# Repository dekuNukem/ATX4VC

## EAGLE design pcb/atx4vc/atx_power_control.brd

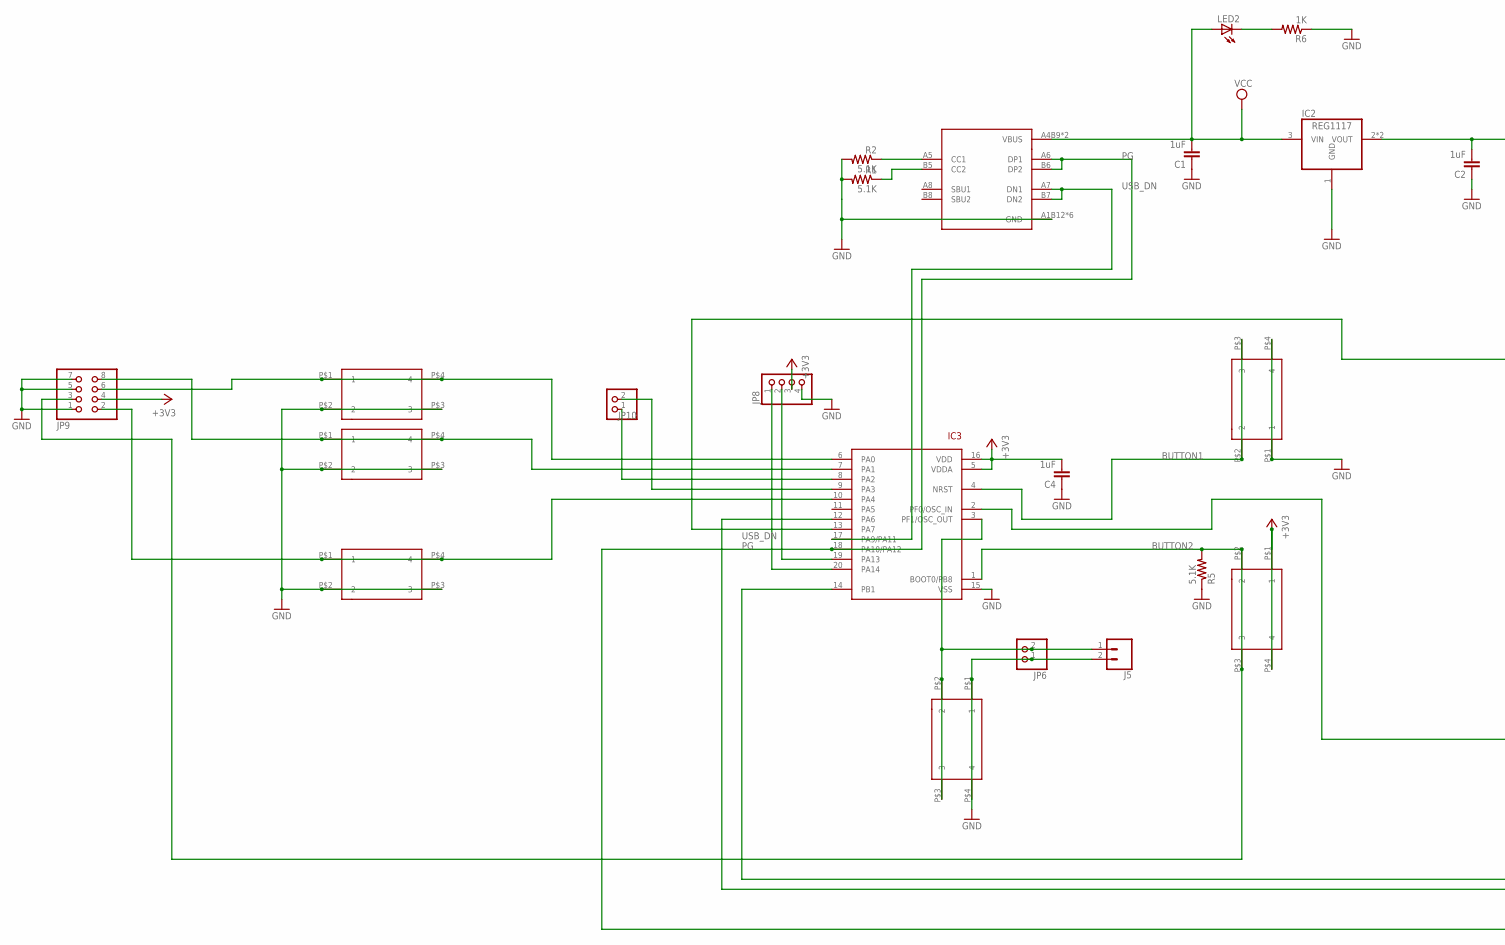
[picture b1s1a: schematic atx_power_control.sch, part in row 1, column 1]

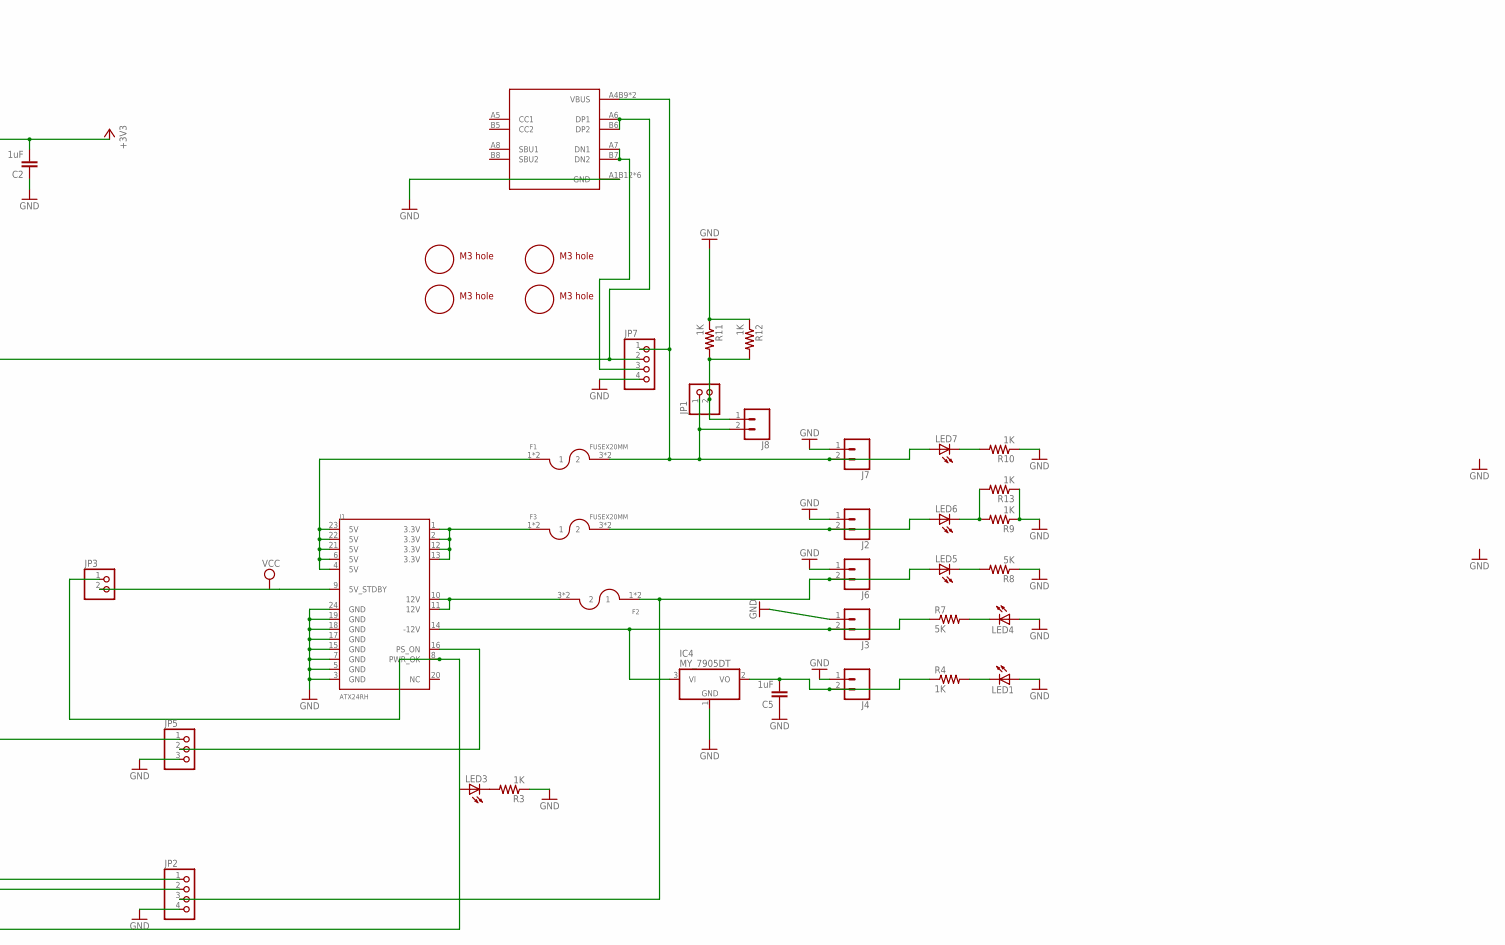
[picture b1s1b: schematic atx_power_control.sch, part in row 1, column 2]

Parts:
C1, C2, C4, C5: 1uF; 0805@1
F1, F2, F3: FUSEX20MM; FUSE_5MM
IC2: REG1117; SOT223
IC3: STM32F042F4; TSSOP20
IC4: MY_7905DT; ADAFRUIT_TO252
J1: ATX24RH; ATX24_RIGHT_ANGLE
J2, J3, J4, J5, J6, J8: CONN_023.5MM; SCREWTERMINAL-3.5MM-2
J7: CONN_023.5MM-NO_SILK; SCREWTERMINAL-3.5MM-2-NS
JP1, JP3, JP6, JP10: PINHD-1X2; 1X02
JP2, JP7, JP8: PINHD-1X4; 1X04
JP5: PINHD-1X3; 1X03
JP9: PINHD-2X4; 2X04
LED1, LED2, LED3, LED4, LED5, LED6, LED7: LEDCHIP-LED0805; CHIP-LED0805
R1, R2, R5: 5.1K; 0805
R3, R4, R6, R9, R10, R11, R12, R13: 1K; 0805
R7, R8: 5K; 0805
SW1, SW2, SW3, SW4, SW5, SW7: 324_SW; 342_SWICH_FOOT
U1, U2: USBC_16P; USBC_16P_FOOT
U$1, U$2, U$3, U$10: M3_MOUNTING_HOLE; M3_MOUNTING_HOLE_PACK

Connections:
+3V3: C2.2, C4.2, IC2.2 (VOUT), IC2.4 (VOUT), IC3.5 (VDDA), IC3.16 (VDD), JP8.3, JP9.4, SW4.P$1 (1), SW4.P$4 (4)
BUTTON1: IC3.4 (NRST), SW3.P$2 (2), SW3.P$3 (3)
BUTTON2: IC3.1 (BOOT0/PB8), JP9.3, R5.2, SW4.P$2 (2), SW4.P$3 (3)
GND: C1.1, C2.1, C4.1, C5.1, IC2.1 (GND), IC3.15 (VSS), IC4.1 (GND), J1.3 (GND), J1.5 (GND), J1.7 (GND), J1.15 (GND), J1.17 (GND), J1.18 (GND), J1.19 (GND), J1.24 (GND), J2.1, J3.1, J4.1, J5.2, J6.1, J7.1, JP2.4, JP5.3, JP6.1, JP7.4, JP8.4, JP9.1, JP9.5, JP9.7, LED1.A, LED4.A, R1.2, R2.2, R3.1, R5.1, R6.1, R8.1, R9.1, R10.1, R11.1, R12.1, R13.1, SW1.P$1 (1), SW1.P$4 (4), SW2.P$2 (2), SW2.P$3 (3), SW3.P$1 (1), SW3.P$4 (4), SW5.P$2 (2), SW5.P$3 (3), SW7.P$2 (2), SW7.P$3 (3), U1.A1B12 (GND), U1.B11A12 (GND), U1.P$13 (GND), U1.P$14 (GND), U1.P$15 (GND), U1.P$16 (GND), U2.A1B12 (GND), U2.B11A12 (GND), U2.P$13 (GND), U2.P$14 (GND), U2.P$15 (GND), U2.P$16 (GND)
unnamed: LED3.C, R3.2
unnamed: IC4.3 (VI), J1.14 (-12V), J3.2, R7.1
unnamed: IC3.20 (PA14), JP8.1
unnamed: IC3.19 (PA13), JP8.2
unnamed: LED1.C, R4.2
unnamed: IC3.12 (PA6), JP2.2
unnamed: IC3.14 (PB1), JP2.1
unnamed: LED4.C, R7.2
unnamed: LED5.C, R8.2
unnamed: F1.1, F1.2 (1), J1.4 (5V), J1.6 (5V), J1.21 (5V), J1.22 (5V), J1.23 (5V)
unnamed: C5.2, IC4.2 (VO), J4.2, R4.1
unnamed: IC3.9 (PA3), JP10.2
unnamed: IC3.6 (PA0), JP9.6, SW2.P$1 (1), SW2.P$4 (4)
unnamed: F3.1, F3.2 (1), J1.1 (3.3V), J1.2 (3.3V), J1.12 (3.3V), J1.13 (3.3V)
unnamed: F2.1, F2.2 (1), J6.2, JP2.3, LED5.A
unnamed: J8.1, JP1.2, R11.2, R12.2
unnamed: LED6.C, R9.2, R13.2
unnamed: F3.3 (2), F3.4 (2), J2.2, LED6.A
unnamed: LED7.C, R10.2
unnamed: F2.3 (2), F2.4 (2), J1.10 (12V), J1.11 (12V)
unnamed: IC3.7 (PA1), JP9.8, SW5.P$1 (1), SW5.P$4 (4)
unnamed: IC3.8 (PA2), JP10.1
unnamed: IC3.2 (PF0/OSC_IN), JP5.1
unnamed: J1.16 (PS_ON), JP5.2
unnamed: IC3.3 (PF1/OSC_OUT), J5.1, JP6.2, SW1.P$2 (2), SW1.P$3 (3)
unnamed: IC3.10 (PA4), JP9.2, SW7.P$1 (1), SW7.P$4 (4)
unnamed: LED2.C, R6.2
unnamed: F1.3 (2), F1.4 (2), J7.2, J8.2, JP1.1, JP7.1, LED7.A, U1.A4B9 (VBUS), U1.B4A9 (VBUS)
unnamed: R1.1, U2.B5 (CC2)
unnamed: R2.1, U2.A5 (CC1)
unnamed: IC3.13 (PA7), JP7.2, U1.A6 (DP1), U1.B6 (DP2)
unnamed: JP7.3, U1.A7 (DN1), U1.B7 (DN2)
PG: IC3.18 (PA10/PA12), J1.8 (PWR_OK), JP3.1, LED3.A, U2.A6 (DP1), U2.B6 (DP2)
USB_DN: IC3.17 (PA9/PA11), U2.A7 (DN1), U2.B7 (DN2)
VCC: C1.2, IC2.3 (VIN), J1.9 (5V_STDBY), JP3.2, LED2.A, U2.A4B9 (VBUS), U2.B4A9 (VBUS)

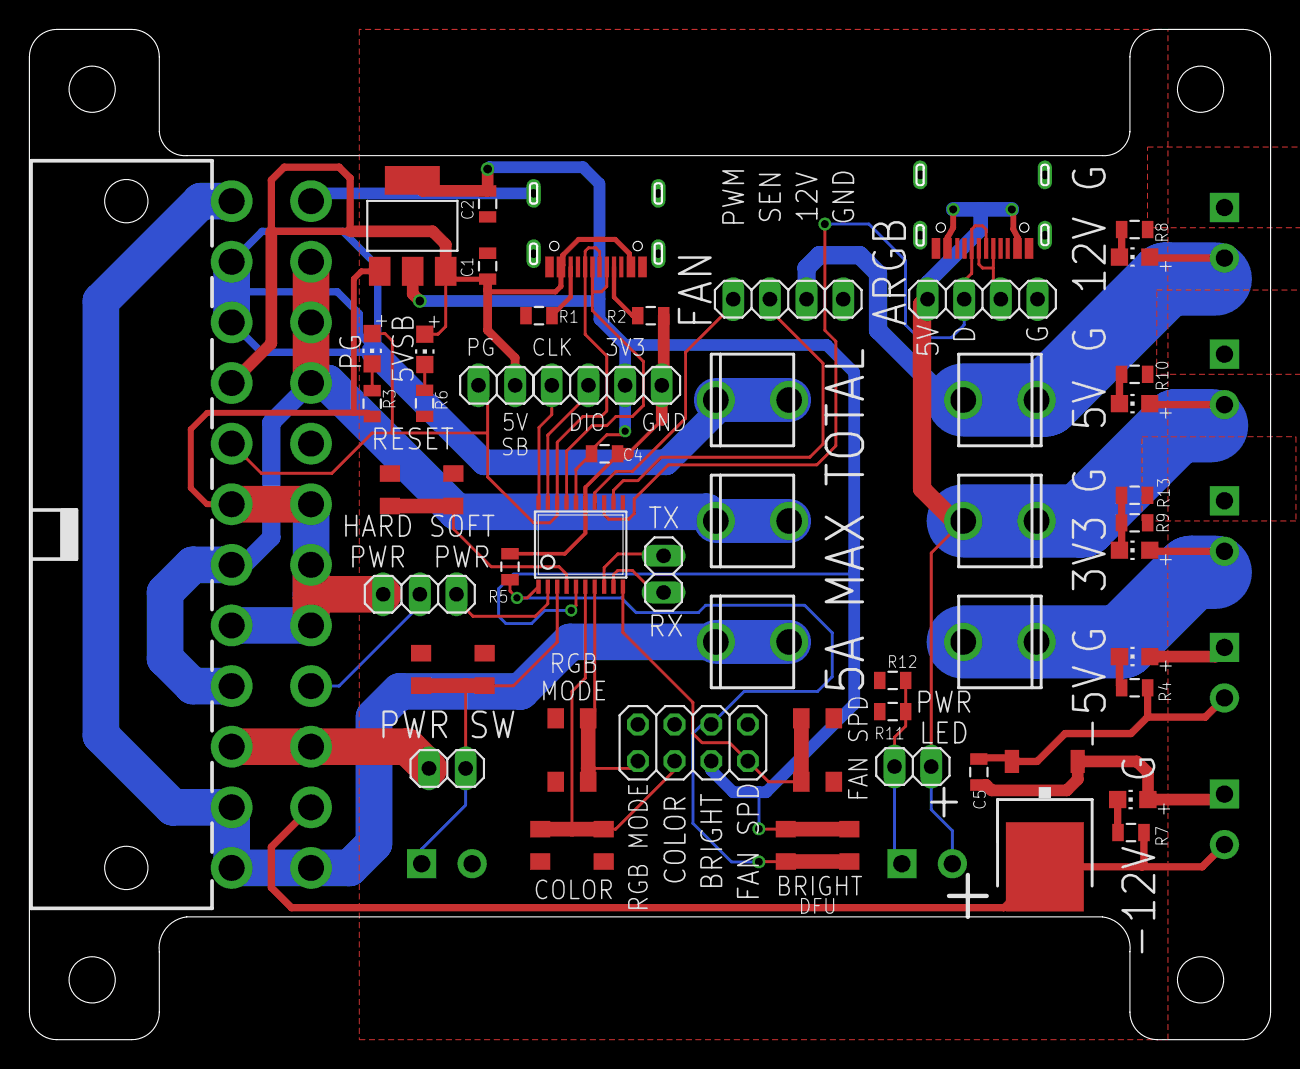
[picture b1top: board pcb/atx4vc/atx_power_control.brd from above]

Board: 2 copper layers, 86.0 x 70.0 mm, 59 parts (0 on the bottom side), 39 nets.

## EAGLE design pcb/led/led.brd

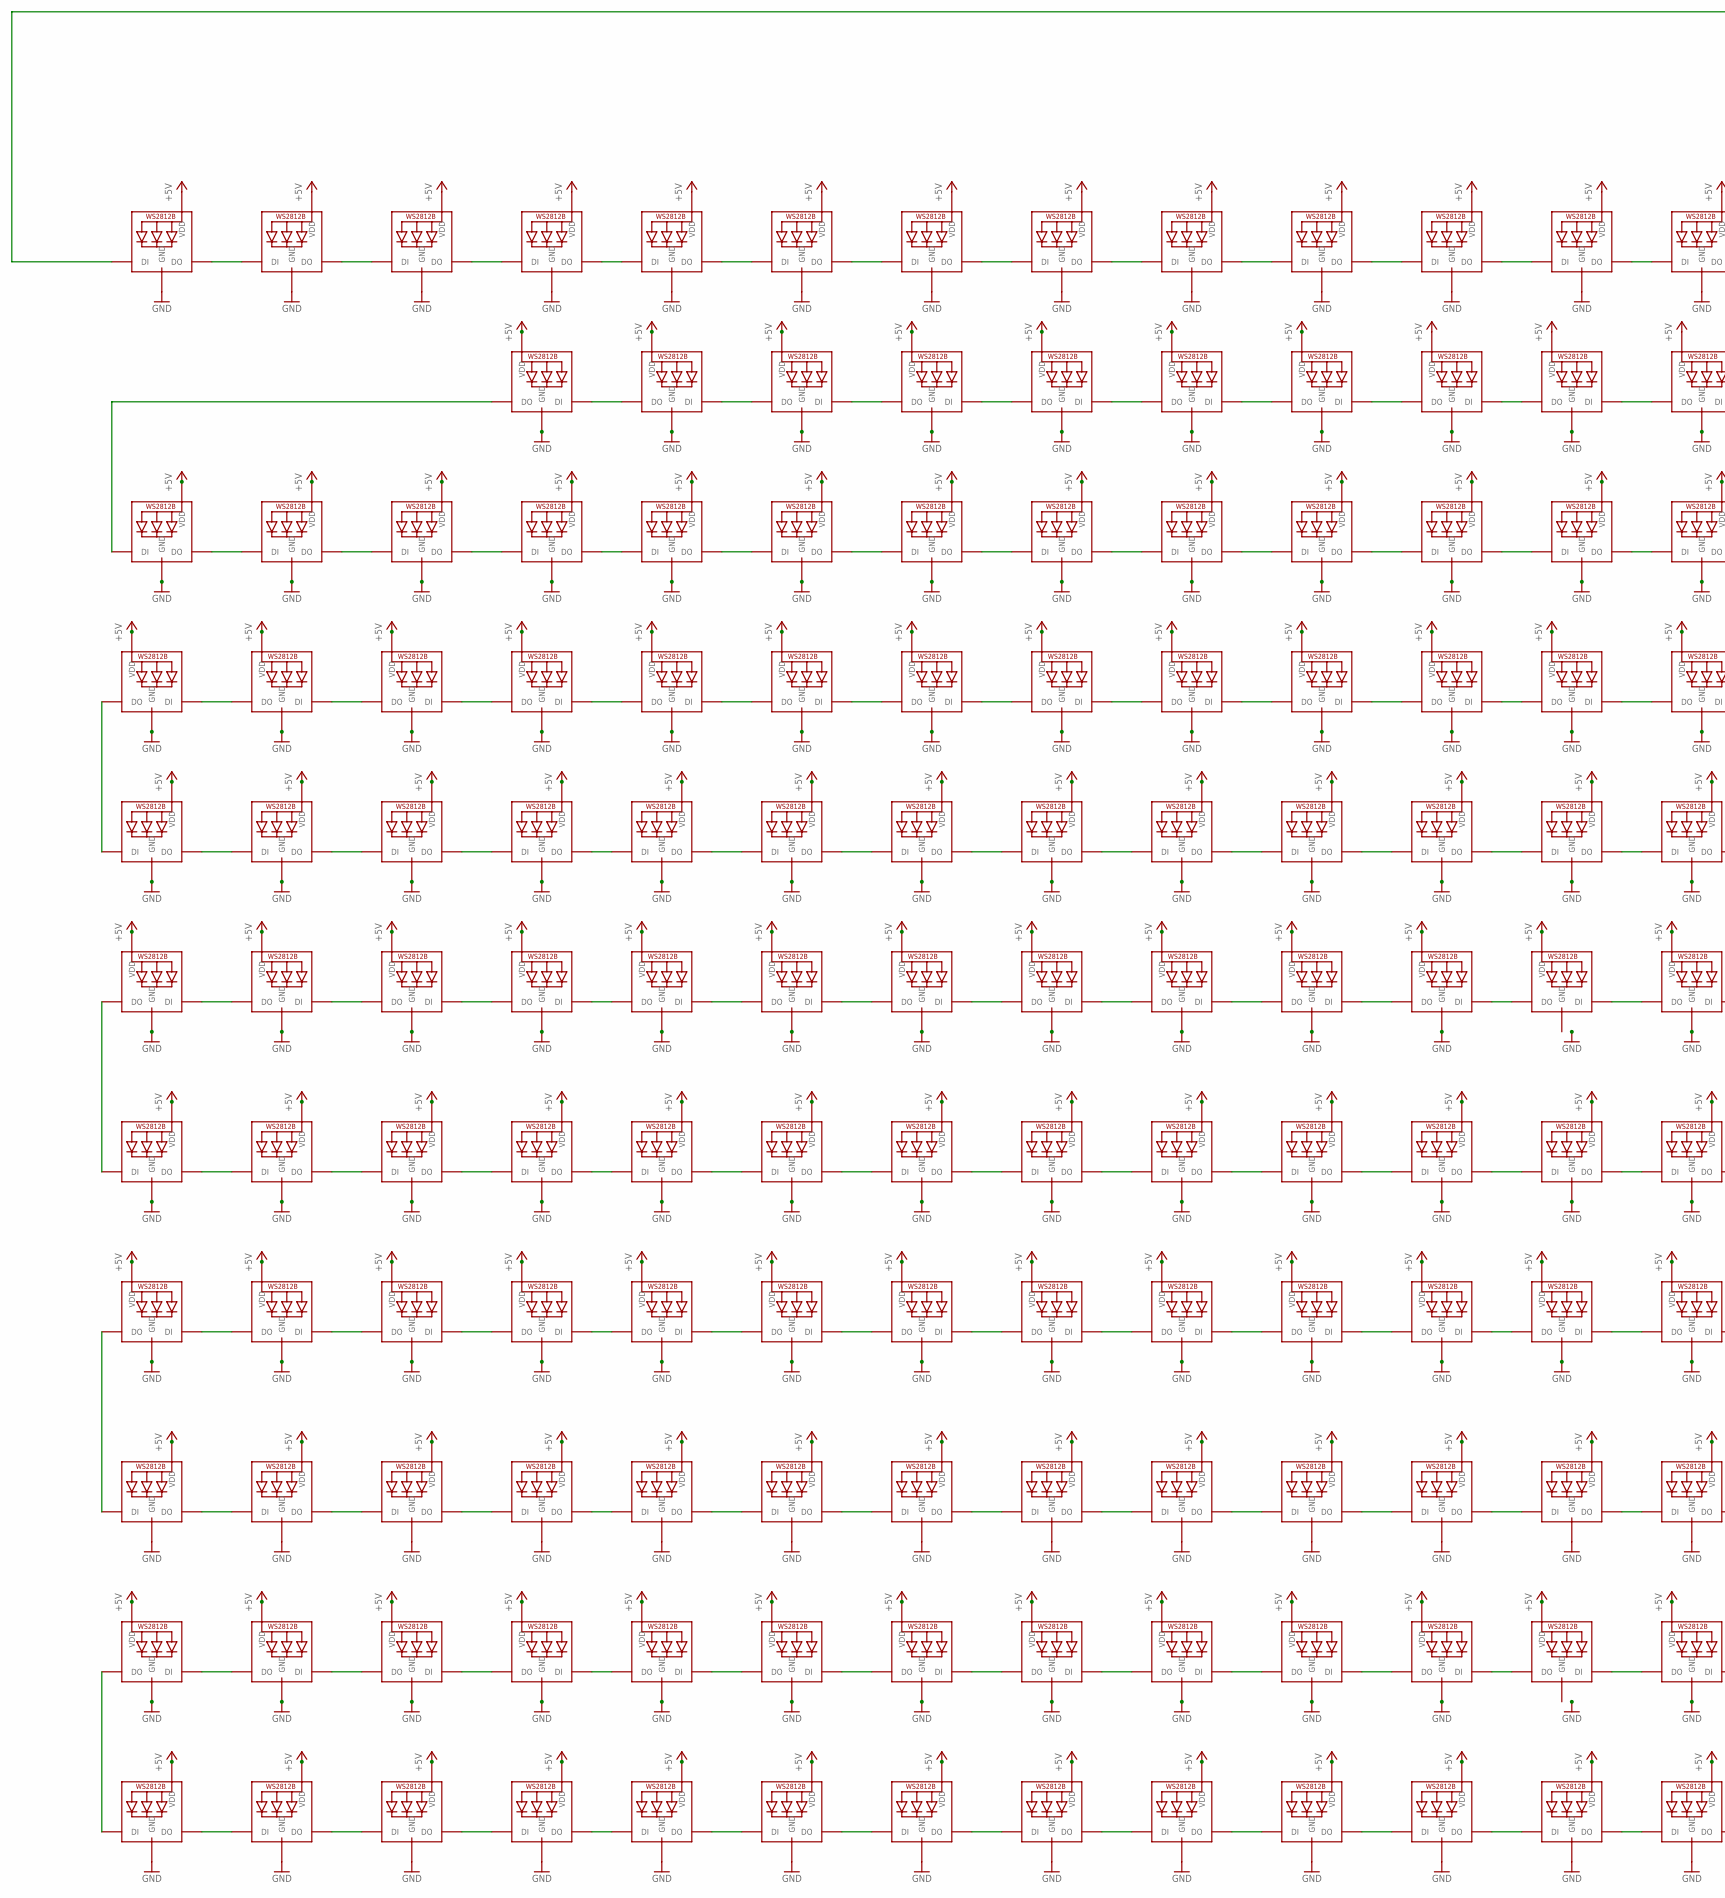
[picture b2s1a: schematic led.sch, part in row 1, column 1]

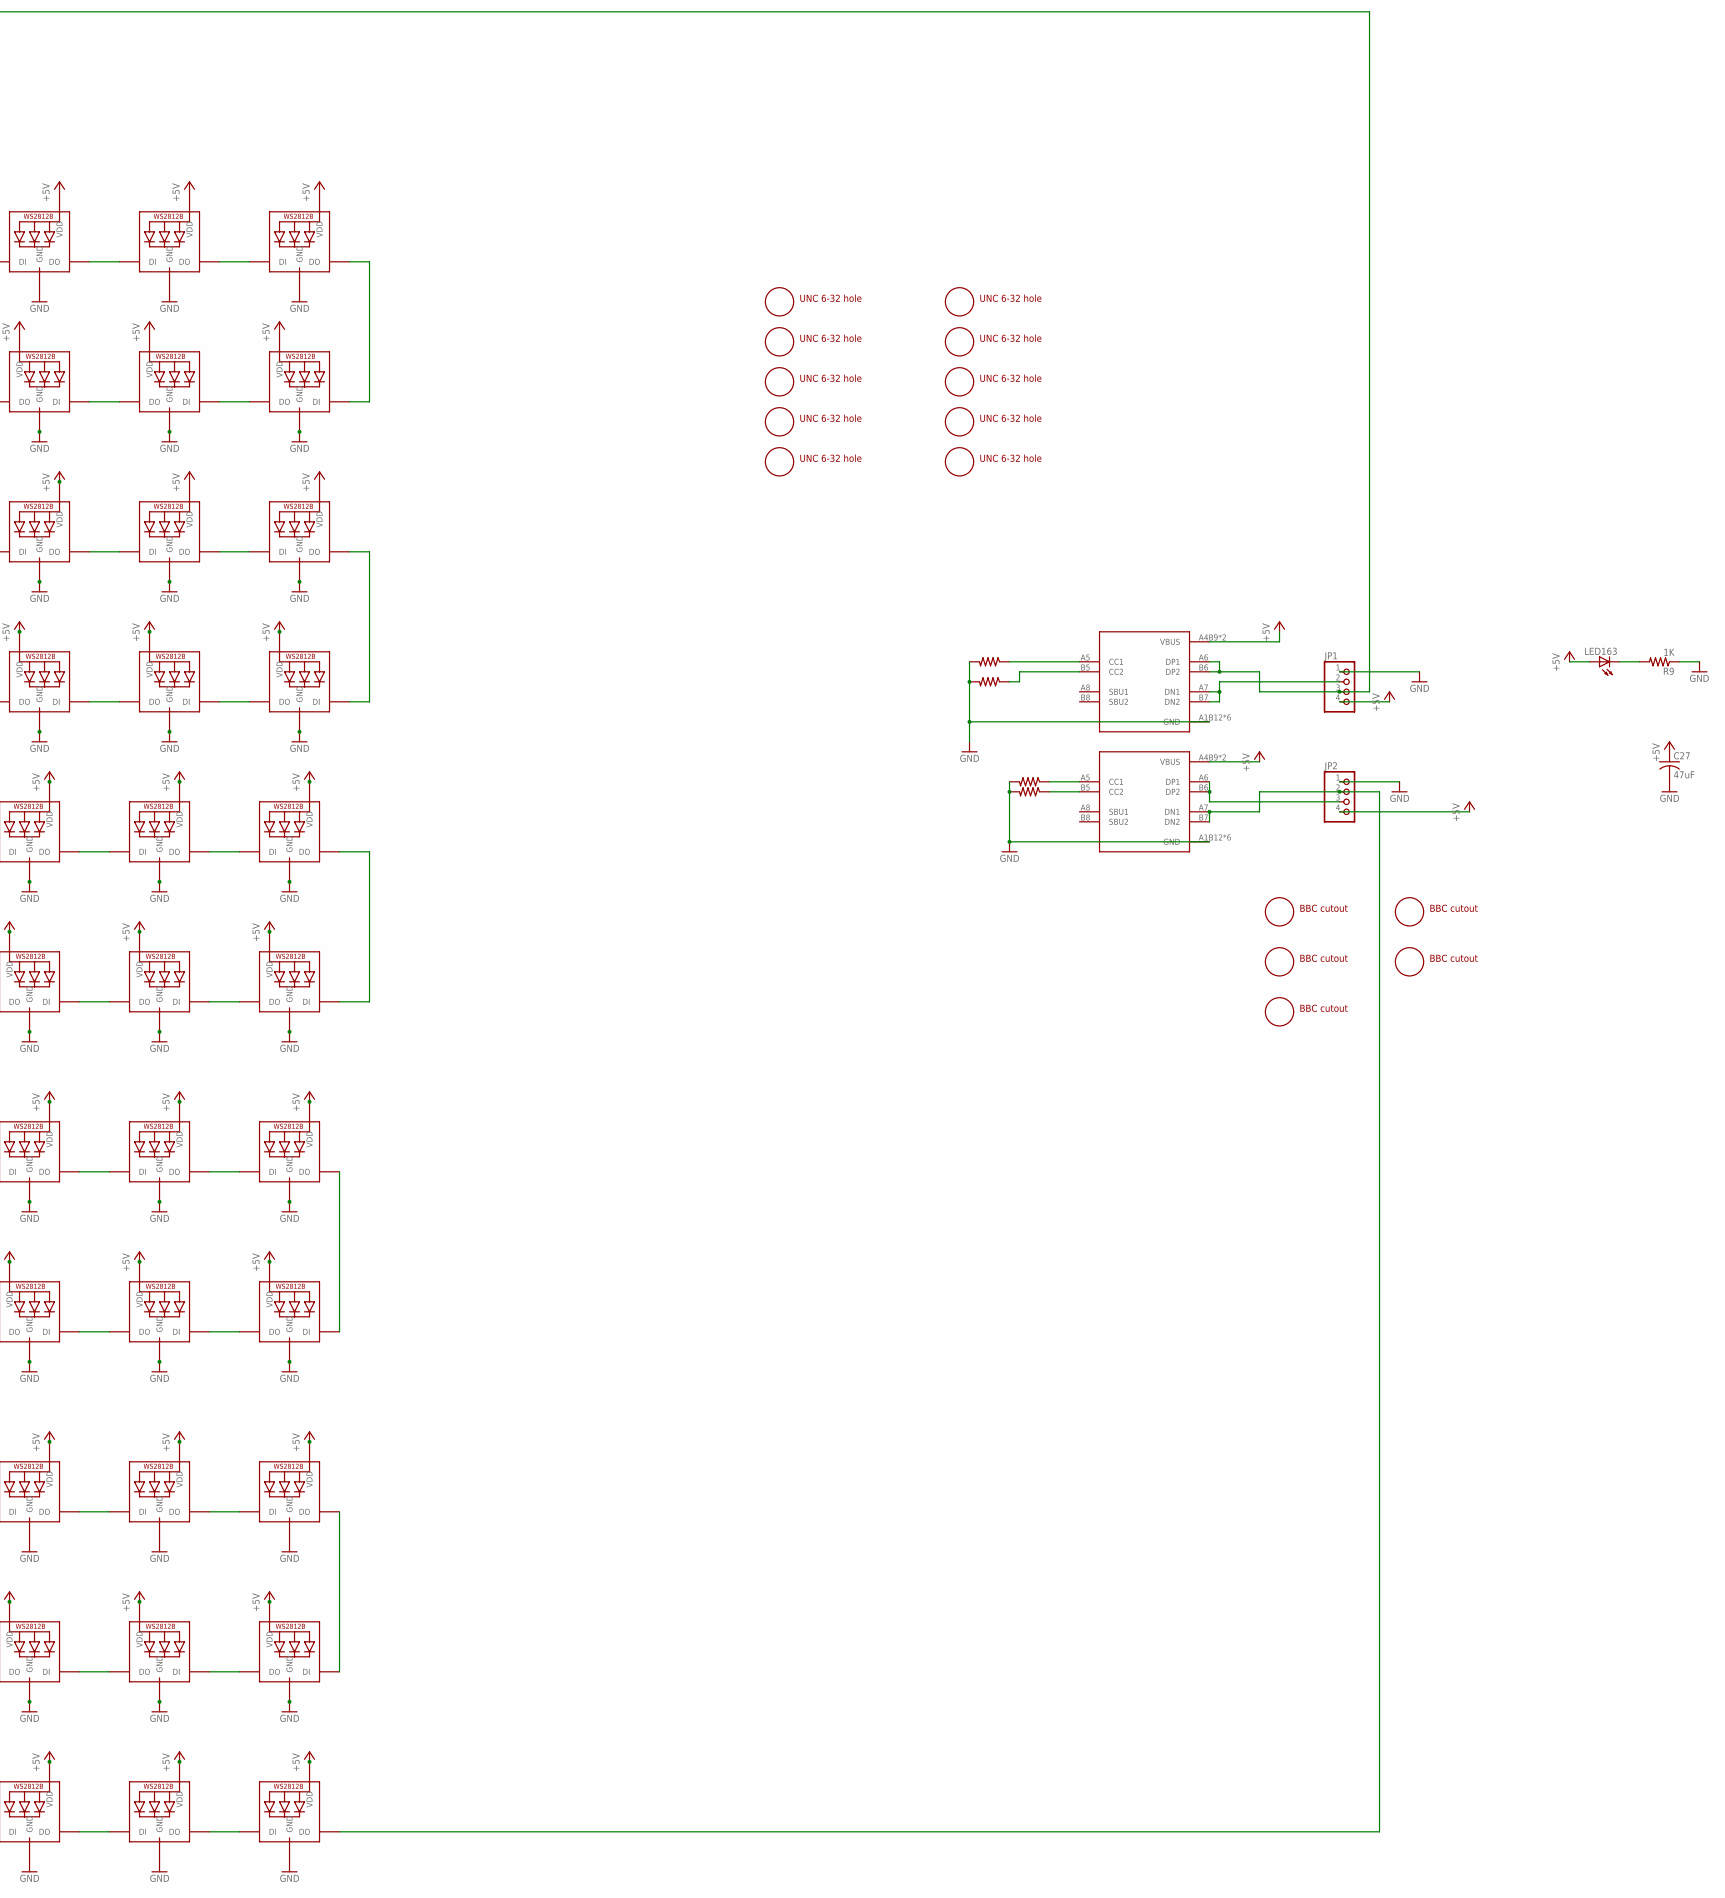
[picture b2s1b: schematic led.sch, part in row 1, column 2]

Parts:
C27: 47uF; C1210
JP1, JP2: PINHD-1X4; 1X04
LED1, LED2, LED3, LED4, LED5, LED6, LED7, LED8, LED9, LED10, LED11, LED12, LED13, LED14, LED15, LED16, LED17, LED18, LED19, LED20, LED21, LED22, LED23, LED24, LED25, LED26, LED27, LED28, LED29, LED30, LED31, LED32, LED33, LED34, LED35, LED36, LED37, LED38, LED39, LED40, LED41, LED42, LED43, LED44, LED45, LED46, LED47, LED48, LED49, LED50, LED51, LED52, LED53, LED54, LED55, LED56, LED57, LED58, LED59, LED60, LED61, LED62, LED63, LED64, LED65, LED66, LED67, LED68, LED69, LED70, LED71, LED72, LED73, LED74, LED75, LED76, LED77, LED78, LED79, LED80, LED81, LED82, LED83, LED84, LED85, LED86, LED87, LED88, LED89, LED90, LED91, LED92, LED93, LED94, LED95, LED96, LED97, LED98, LED99, LED100, LED101, LED102, LED103, LED104, LED105, LED106, LED107, LED108, LED109, LED110, LED111, LED112, LED113, LED114, LED115, LED116, LED117, LED118, LED119, LED120, LED121, LED122, LED123, LED124, LED125, LED126, LED127, LED128, LED129, LED130, LED131, LED132, LED133, LED134, LED135, LED136, LED137, LED138, LED139, LED140, LED141, LED142, LED143, LED144, LED145, LED146, LED147, LED148, LED149, LED150, LED151, LED152, LED153, LED154, LED155, LED156, LED157, LED158, LED159, LED160, LED161, LED162: WS2812B; REVERSE_MNT
LED163: LEDCHIP-LED0805; CHIP-LED0805
R1, R2, R3, R4: 5.1K; 0805
R9: 1K; 0805
U1, U2: USBC_16P; USBC_16P_FOOT
U$1, U$2, U$3, U$4, U$5, U$6, U$7, U$8, U$9, U$10: MOTHERBOARD_MOUNTING_HOLE; MOTEHRBOARD_MOUNTING_HOLE
U$11, U$12, U$13, U$14, U$15: BBC_CUTOUT; BBC_MOUNTING_HOLE_CUTOUT

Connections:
+5V: C27.1, JP1.4, JP2.4, LED1.VDD, LED2.VDD, LED3.VDD, LED4.VDD, LED5.VDD, LED6.VDD, LED7.VDD, LED8.VDD, LED9.VDD, LED10.VDD, LED11.VDD, LED12.VDD, LED13.VDD, LED14.VDD, LED15.VDD, LED16.VDD, LED17.VDD, LED18.VDD, LED19.VDD, LED20.VDD, LED21.VDD, LED22.VDD, LED23.VDD, LED24.VDD, LED25.VDD, LED26.VDD, LED27.VDD, LED28.VDD, LED29.VDD, LED30.VDD, LED31.VDD, LED32.VDD, LED33.VDD, LED34.VDD, LED35.VDD, LED36.VDD, LED37.VDD, LED38.VDD, LED39.VDD, LED40.VDD, LED41.VDD, LED42.VDD, LED43.VDD, LED44.VDD, LED45.VDD, LED46.VDD, LED47.VDD, LED48.VDD, LED49.VDD, LED50.VDD, LED51.VDD, LED52.VDD, LED53.VDD, LED54.VDD, LED55.VDD, LED56.VDD, LED57.VDD, LED58.VDD, LED59.VDD, LED60.VDD, LED61.VDD, LED62.VDD, LED63.VDD, LED64.VDD, LED65.VDD, LED66.VDD, LED67.VDD, LED68.VDD, LED69.VDD, LED70.VDD, LED71.VDD, LED72.VDD, LED73.VDD, LED74.VDD, LED75.VDD, LED76.VDD, LED77.VDD, LED78.VDD, LED79.VDD, LED80.VDD, LED81.VDD, LED82.VDD, LED83.VDD, LED84.VDD, LED85.VDD, LED86.VDD, LED87.VDD, LED88.VDD, LED89.VDD, LED90.VDD, LED91.VDD, LED92.VDD, LED93.VDD, LED94.VDD, LED95.VDD, LED96.VDD, LED97.VDD, LED98.VDD, LED99.VDD, LED100.VDD, LED101.VDD, LED102.VDD, LED103.VDD, LED104.VDD, LED105.VDD, LED106.VDD, LED107.VDD, LED108.VDD, LED109.VDD, LED110.VDD, LED111.VDD, LED112.VDD, LED113.VDD, LED114.VDD, LED115.VDD, LED116.VDD, LED117.VDD, LED118.VDD, LED119.VDD, LED120.VDD, LED121.VDD, LED122.VDD, LED123.VDD, LED124.VDD, LED125.VDD, LED126.VDD, LED127.VDD, LED128.VDD, LED129.VDD, LED130.VDD, LED131.VDD, LED132.VDD, LED133.VDD, LED134.VDD, LED135.VDD, LED136.VDD, LED137.VDD, LED138.VDD, LED139.VDD, LED140.VDD, LED141.VDD, LED142.VDD, LED143.VDD, LED144.VDD, LED145.VDD, LED146.VDD, LED147.VDD, LED148.VDD, LED149.VDD, LED150.VDD, LED151.VDD, LED152.VDD, LED153.VDD, LED154.VDD, LED155.VDD, LED156.VDD, LED157.VDD, LED158.VDD, LED159.VDD, LED160.VDD, LED161.VDD, LED162.VDD, LED163.A, U1.A4B9 (VBUS), U1.B4A9 (VBUS), U2.A4B9 (VBUS), U2.B4A9 (VBUS)
GND: C27.2, JP1.1, JP2.1, LED1.GND, LED2.GND, LED3.GND, LED4.GND, LED5.GND, LED6.GND, LED7.GND, LED8.GND, LED9.GND, LED10.GND, LED11.GND, LED12.GND, LED13.GND, LED14.GND, LED15.GND, LED16.GND, LED17.GND, LED18.GND, LED19.GND, LED20.GND, LED21.GND, LED22.GND, LED23.GND, LED24.GND, LED25.GND, LED26.GND, LED27.GND, LED28.GND, LED29.GND, LED30.GND, LED31.GND, LED32.GND, LED33.GND, LED34.GND, LED35.GND, LED36.GND, LED37.GND, LED38.GND, LED39.GND, LED40.GND, LED41.GND, LED42.GND, LED43.GND, LED44.GND, LED45.GND, LED46.GND, LED47.GND, LED48.GND, LED49.GND, LED50.GND, LED51.GND, LED52.GND, LED53.GND, LED54.GND, LED55.GND, LED56.GND, LED57.GND, LED58.GND, LED59.GND, LED60.GND, LED61.GND, LED62.GND, LED63.GND, LED64.GND, LED65.GND, LED66.GND, LED67.GND, LED68.GND, LED69.GND, LED70.GND, LED71.GND, LED72.GND, LED73.GND, LED74.GND, LED75.GND, LED76.GND, LED77.GND, LED78.GND, LED79.GND, LED80.GND, LED81.GND, LED82.GND, LED83.GND, LED84.GND, LED85.GND, LED86.GND, LED87.GND, LED88.GND, LED89.GND, LED90.GND, LED91.GND, LED92.GND, LED93.GND, LED94.GND, LED95.GND, LED96.GND, LED97.GND, LED98.GND, LED99.GND, LED100.GND, LED101.GND, LED102.GND, LED103.GND, LED104.GND, LED105.GND, LED106.GND, LED107.GND, LED108.GND, LED109.GND, LED110.GND, LED111.GND, LED112.GND, LED113.GND, LED114.GND, LED115.GND, LED116.GND, LED117.GND, LED118.GND, LED119.GND, LED120.GND, LED121.GND, LED122.GND, LED123.GND, LED124.GND, LED125.GND, LED126.GND, LED127.GND, LED128.GND, LED129.GND, LED130.GND, LED131.GND, LED132.GND, LED133.GND, LED134.GND, LED135.GND, LED136.GND, LED137.GND, LED138.GND, LED139.GND, LED140.GND, LED141.GND, LED142.GND, LED143.GND, LED144.GND, LED145.GND, LED146.GND, LED147.GND, LED148.GND, LED149.GND, LED150.GND, LED151.GND, LED152.GND, LED153.GND, LED154.GND, LED155.GND, LED156.GND, LED157.GND, LED158.GND, LED159.GND, LED160.GND, LED161.GND, LED162.GND, R1.2, R2.2, R3.2, R4.2, R9.1, U1.A1B12 (GND), U1.B11A12 (GND), U1.P$13 (GND), U1.P$14 (GND), U1.P$15 (GND), U1.P$16 (GND), U2.A1B12 (GND), U2.B11A12 (GND), U2.P$13 (GND), U2.P$14 (GND), U2.P$15 (GND), U2.P$16 (GND)
unnamed: LED1.DOUT (DO), LED2.DIN (DI)
unnamed: LED2.DOUT (DO), LED3.DIN (DI)
unnamed: LED3.DOUT (DO), LED4.DIN (DI)
unnamed: LED4.DOUT (DO), LED5.DIN (DI)
unnamed: LED5.DOUT (DO), LED6.DIN (DI)
unnamed: LED6.DOUT (DO), LED7.DIN (DI)
unnamed: R3.1, U1.A5 (CC1)
unnamed: LED8.DOUT (DO), LED9.DIN (DI)
unnamed: LED9.DOUT (DO), LED10.DIN (DI)
unnamed: LED10.DOUT (DO), LED11.DIN (DI)
unnamed: LED11.DOUT (DO), LED12.DIN (DI)
unnamed: LED12.DOUT (DO), LED13.DIN (DI)
unnamed: LED13.DOUT (DO), LED14.DIN (DI)
unnamed: LED14.DOUT (DO), LED15.DIN (DI)
unnamed: LED15.DOUT (DO), LED16.DIN (DI)
unnamed: LED16.DOUT (DO), LED17.DIN (DI)
unnamed: LED17.DOUT (DO), LED18.DIN (DI)
unnamed: LED18.DOUT (DO), LED19.DIN (DI)
unnamed: LED19.DOUT (DO), LED20.DIN (DI)
unnamed: LED20.DOUT (DO), LED21.DIN (DI)
unnamed: LED21.DOUT (DO), LED22.DIN (DI)
unnamed: LED22.DOUT (DO), LED23.DIN (DI)
unnamed: LED23.DOUT (DO), LED24.DIN (DI)
unnamed: LED24.DOUT (DO), LED25.DIN (DI)
unnamed: LED25.DOUT (DO), LED26.DIN (DI)
unnamed: LED26.DOUT (DO), LED27.DIN (DI)
unnamed: LED28.DOUT (DO), LED29.DIN (DI)
unnamed: LED29.DOUT (DO), LED30.DIN (DI)
unnamed: LED30.DOUT (DO), LED31.DIN (DI)
unnamed: LED31.DOUT (DO), LED32.DIN (DI)
unnamed: R1.1, U2.B5 (CC2)
unnamed: LED32.DOUT (DO), LED33.DIN (DI)
unnamed: R2.1, U2.A5 (CC1)
unnamed: LED33.DOUT (DO), LED34.DIN (DI)
unnamed: LED34.DOUT (DO), LED35.DIN (DI)
unnamed: LED35.DOUT (DO), LED36.DIN (DI)
unnamed: LED36.DOUT (DO), LED37.DIN (DI)
unnamed: LED37.DOUT (DO), LED38.DIN (DI)
unnamed: LED38.DOUT (DO), LED39.DIN (DI)
unnamed: LED39.DOUT (DO), LED40.DIN (DI)
unnamed: LED40.DOUT (DO), LED41.DIN (DI)
unnamed: LED41.DOUT (DO), LED42.DIN (DI)
unnamed: LED42.DOUT (DO), LED43.DIN (DI)
unnamed: LED27.DOUT (DO), LED28.DIN (DI)
unnamed: LED54.DOUT (DO), LED55.DIN (DI)
unnamed: LED43.DOUT (DO), LED44.DIN (DI)
unnamed: LED44.DOUT (DO), LED45.DIN (DI)
unnamed: LED45.DOUT (DO), LED46.DIN (DI)
unnamed: LED46.DOUT (DO), LED47.DIN (DI)
unnamed: LED47.DOUT (DO), LED48.DIN (DI)
unnamed: LED48.DOUT (DO), LED49.DIN (DI)
unnamed: LED49.DOUT (DO), LED50.DIN (DI)
unnamed: LED50.DOUT (DO), LED51.DIN (DI)
unnamed: LED51.DOUT (DO), LED52.DIN (DI)
unnamed: LED52.DOUT (DO), LED53.DIN (DI)
unnamed: LED53.DOUT (DO), LED54.DIN (DI)
unnamed: LED55.DOUT (DO), LED56.DIN (DI)
unnamed: LED56.DOUT (DO), LED57.DIN (DI)
unnamed: LED58.DOUT (DO), LED59.DIN (DI)
unnamed: LED59.DOUT (DO), LED60.DIN (DI)
unnamed: LED60.DOUT (DO), LED61.DIN (DI)
unnamed: LED61.DOUT (DO), LED62.DIN (DI)
unnamed: LED62.DOUT (DO), LED63.DIN (DI)
unnamed: LED63.DOUT (DO), LED64.DIN (DI)
unnamed: LED64.DOUT (DO), LED65.DIN (DI)
unnamed: LED65.DOUT (DO), LED66.DIN (DI)
unnamed: LED66.DOUT (DO), LED67.DIN (DI)
unnamed: LED67.DOUT (DO), LED68.DIN (DI)
unnamed: LED68.DOUT (DO), LED69.DIN (DI)
unnamed: LED69.DOUT (DO), LED70.DIN (DI)
unnamed: LED70.DOUT (DO), LED71.DIN (DI)
unnamed: LED71.DOUT (DO), LED72.DIN (DI)
unnamed: LED57.DOUT (DO), LED58.DIN (DI)
unnamed: LED73.DOUT (DO), LED74.DIN (DI)
unnamed: LED74.DOUT (DO), LED75.DIN (DI)
unnamed: LED75.DOUT (DO), LED76.DIN (DI)
unnamed: LED76.DOUT (DO), LED77.DIN (DI)
unnamed: LED77.DOUT (DO), LED78.DIN (DI)
unnamed: LED78.DOUT (DO), LED79.DIN (DI)
unnamed: LED79.DOUT (DO), LED80.DIN (DI)
unnamed: LED80.DOUT (DO), LED81.DIN (DI)
unnamed: LED81.DOUT (DO), LED82.DIN (DI)
unnamed: LED82.DOUT (DO), LED83.DIN (DI)
unnamed: LED83.DOUT (DO), LED84.DIN (DI)
unnamed: LED84.DOUT (DO), LED85.DIN (DI)
unnamed: LED85.DOUT (DO), LED86.DIN (DI)
unnamed: LED86.DOUT (DO), LED87.DIN (DI)
unnamed: LED72.DOUT (DO), LED73.DIN (DI)
unnamed: LED88.DOUT (DO), LED89.DIN (DI)
unnamed: LED89.DOUT (DO), LED90.DIN (DI)
unnamed: LED90.DOUT (DO), LED91.DIN (DI)
unnamed: LED91.DOUT (DO), LED92.DIN (DI)
unnamed: LED92.DOUT (DO), LED93.DIN (DI)
unnamed: LED93.DOUT (DO), LED94.DIN (DI)
unnamed: LED94.DOUT (DO), LED95.DIN (DI)
unnamed: LED95.DOUT (DO), LED96.DIN (DI)
unnamed: LED96.DOUT (DO), LED97.DIN (DI)
unnamed: LED97.DOUT (DO), LED98.DIN (DI)
unnamed: LED98.DOUT (DO), LED99.DIN (DI)
unnamed: LED99.DOUT (DO), LED100.DIN (DI)
unnamed: LED100.DOUT (DO), LED101.DIN (DI)
unnamed: LED101.DOUT (DO), LED102.DIN (DI)
unnamed: LED87.DOUT (DO), LED88.DIN (DI)
unnamed: LED103.DOUT (DO), LED104.DIN (DI)
unnamed: LED104.DOUT (DO), LED105.DIN (DI)
unnamed: LED105.DOUT (DO), LED106.DIN (DI)
unnamed: LED106.DOUT (DO), LED107.DIN (DI)
unnamed: LED107.DOUT (DO), LED108.DIN (DI)
unnamed: LED108.DOUT (DO), LED109.DIN (DI)
unnamed: LED109.DOUT (DO), LED110.DIN (DI)
unnamed: LED110.DOUT (DO), LED111.DIN (DI)
unnamed: LED111.DOUT (DO), LED112.DIN (DI)
unnamed: LED112.DOUT (DO), LED113.DIN (DI)
unnamed: LED113.DOUT (DO), LED114.DIN (DI)
unnamed: LED114.DOUT (DO), LED115.DIN (DI)
unnamed: LED115.DOUT (DO), LED116.DIN (DI)
unnamed: LED116.DOUT (DO), LED117.DIN (DI)
unnamed: LED102.DOUT (DO), LED103.DIN (DI)
unnamed: LED118.DOUT (DO), LED119.DIN (DI)
unnamed: LED119.DOUT (DO), LED120.DIN (DI)
unnamed: LED120.DOUT (DO), LED121.DIN (DI)
unnamed: LED121.DOUT (DO), LED122.DIN (DI)
unnamed: LED122.DOUT (DO), LED123.DIN (DI)
unnamed: LED123.DOUT (DO), LED124.DIN (DI)
unnamed: LED124.DOUT (DO), LED125.DIN (DI)
unnamed: LED125.DOUT (DO), LED126.DIN (DI)
unnamed: LED126.DOUT (DO), LED127.DIN (DI)
unnamed: LED127.DOUT (DO), LED128.DIN (DI)
unnamed: LED128.DOUT (DO), LED129.DIN (DI)
unnamed: LED129.DOUT (DO), LED130.DIN (DI)
unnamed: LED130.DOUT (DO), LED131.DIN (DI)
unnamed: LED131.DOUT (DO), LED132.DIN (DI)
unnamed: LED117.DOUT (DO), LED118.DIN (DI)
unnamed: LED133.DOUT (DO), LED134.DIN (DI)
unnamed: LED134.DOUT (DO), LED135.DIN (DI)
unnamed: LED135.DOUT (DO), LED136.DIN (DI)
unnamed: LED136.DOUT (DO), LED137.DIN (DI)
unnamed: LED137.DOUT (DO), LED138.DIN (DI)
unnamed: LED138.DOUT (DO), LED139.DIN (DI)
unnamed: LED139.DOUT (DO), LED140.DIN (DI)
unnamed: LED140.DOUT (DO), LED141.DIN (DI)
unnamed: LED141.DOUT (DO), LED142.DIN (DI)
unnamed: LED142.DOUT (DO), LED143.DIN (DI)
unnamed: LED143.DOUT (DO), LED144.DIN (DI)
unnamed: LED144.DOUT (DO), LED145.DIN (DI)
unnamed: LED145.DOUT (DO), LED146.DIN (DI)
unnamed: LED146.DOUT (DO), LED147.DIN (DI)
unnamed: LED132.DOUT (DO), LED133.DIN (DI)
unnamed: LED148.DOUT (DO), LED149.DIN (DI)
unnamed: LED149.DOUT (DO), LED150.DIN (DI)
unnamed: LED150.DOUT (DO), LED151.DIN (DI)
unnamed: LED151.DOUT (DO), LED152.DIN (DI)
unnamed: LED152.DOUT (DO), LED153.DIN (DI)
unnamed: LED153.DOUT (DO), LED154.DIN (DI)
unnamed: LED154.DOUT (DO), LED155.DIN (DI)
unnamed: LED155.DOUT (DO), LED156.DIN (DI)
unnamed: LED156.DOUT (DO), LED157.DIN (DI)
unnamed: LED157.DOUT (DO), LED158.DIN (DI)
unnamed: LED158.DOUT (DO), LED159.DIN (DI)
unnamed: LED159.DOUT (DO), LED160.DIN (DI)
unnamed: LED160.DOUT (DO), LED161.DIN (DI)
unnamed: LED161.DOUT (DO), LED162.DIN (DI)
unnamed: LED147.DOUT (DO), LED148.DIN (DI)
unnamed: R4.1, U1.B5 (CC2)
unnamed: JP1.3, LED1.DIN (DI), U2.A6 (DP1), U2.B6 (DP2)
unnamed: JP1.2, U2.A7 (DN1), U2.B7 (DN2)
unnamed: JP2.3, U1.A6 (DP1), U1.B6 (DP2)
unnamed: JP2.2, LED162.DOUT (DO), U1.A7 (DN1), U1.B7 (DN2)
unnamed: LED7.DOUT (DO), LED8.DIN (DI)
unnamed: LED163.C, R9.2

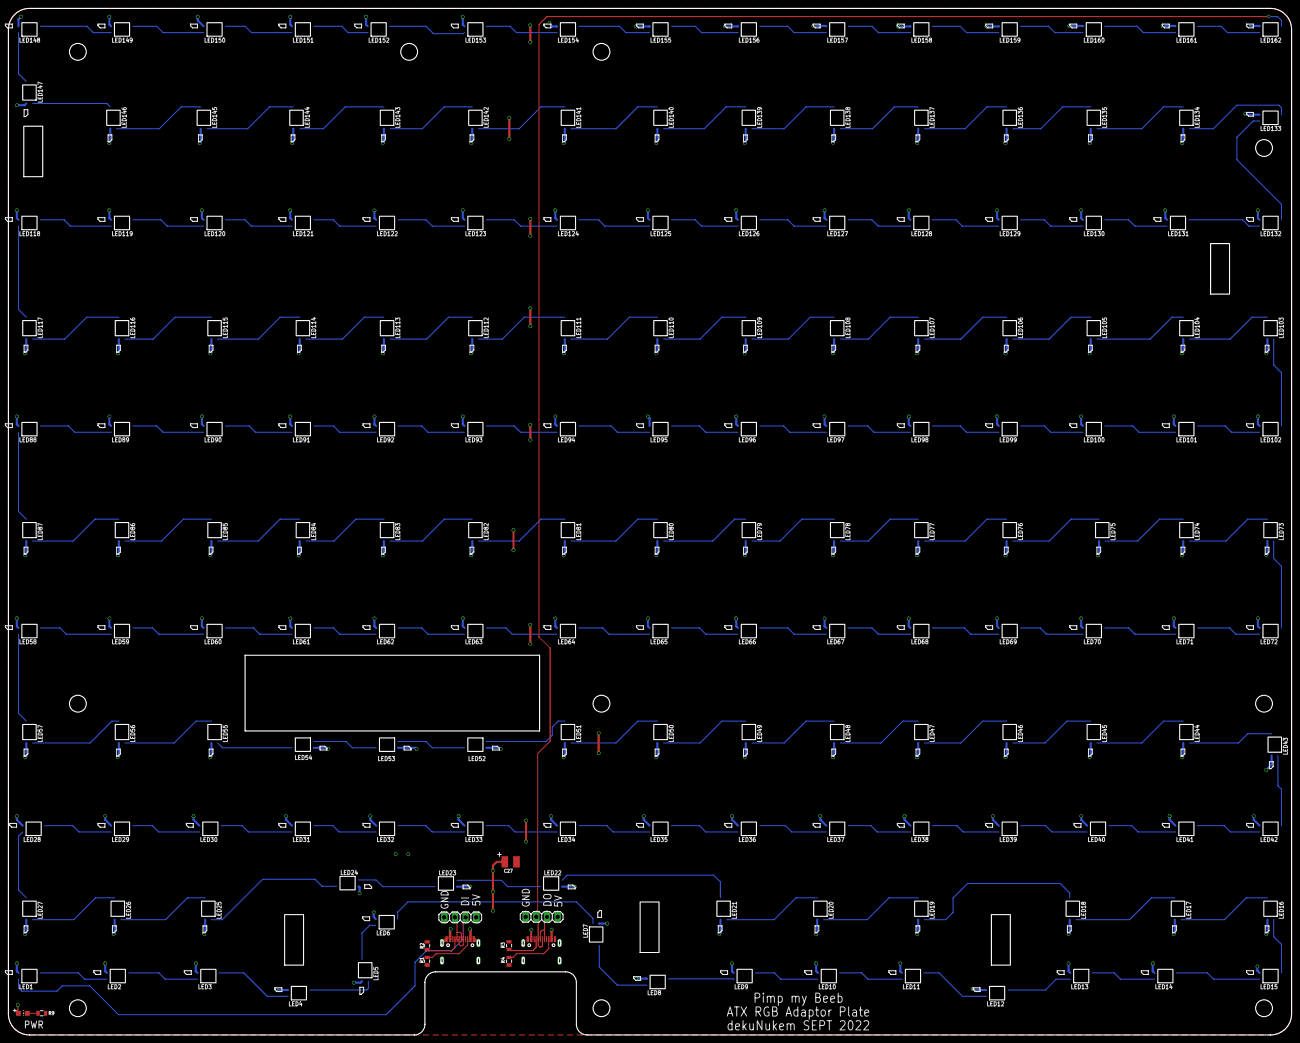
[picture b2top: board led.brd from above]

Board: 2 copper layers, 305.0 x 244.0 mm, 188 parts (0 on the bottom side), 172 nets.

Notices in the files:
parts and their libraries:
SparkFun-Passives: Licensing: Creative Commons ShareAlike 4.0 International - https://creativecommons.org/licenses/by-sa/4.0
SparkFun-Aesthetics: Released under the Creative Commons Attribution Share-Alike 4.0 License
SparkFun-Aesthetics: https://creativecommons.org/licenses/by-sa/4.0
